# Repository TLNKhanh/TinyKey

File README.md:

# TinyKey

A keychain with 49 LEDs on the front and a ten cent MCU doing the work.

I built this because I wanted to find out how much display you can get out of a
microcontroller that costs less than a coffee. The answer, it turns out, is a
49 LED matrix you can scroll text on, carry in your pocket, and charge from
USB-C. The whole thing runs on a CH32V003, the chip WCH sells for about ten
cents.

## Why a ten cent MCU

The CH32V003F4P6 costs about ten cents and it is a real 32-bit part: RISC-V at
48 MHz, 16 kB flash, 2 kB RAM, 18 GPIOs, UART, I2C, SPI, a 10-bit ADC, all in a
TSSOP-20. No USB, no crystal, no external memory, no display controller.

That is the whole appeal. A 7x7 matrix needs 14 pins and 25 bytes of frame
buffer, and the scan has to keep a fixed frame time or the brightness wobbles.
The chip has just enough of everything, so the money goes into the display
instead of the silicon: no driver IC, no series resistors, and the current limit
is the 2 MHz GPIO drive setting. What you pay in return is software, and for a
keychain that is a good trade.

## V1 or V2?

There are two revisions and they are easy to mix up. The photos are V1, the
files in `hardware/` are V2, and V2 has never been manufactured.

| | V1 | V2 |
|---|---|---|
| Shown in | the photos below | the 3D renders and PDFs |
| Board file | `hardware/archive/TinyKeyV1.kicad_pcb` | `hardware/TinyKey.kicad_pcb` |
| Built | yes, it runs | no, files only |
| Size | 40 x 52 mm | 35 x 45.4 mm |
| What changed | the prototype | tighter outline, ground pours redone, DRC clean |

If you want to order a board, use V2. The photos are just what the thing looks
like assembled, with a cell and a keyring on it.

## The hardware

Front: 49 0805 LEDs wired as 7 anode rows and 7 cathode columns, 14 GPIOs in
total. Back: the MCU, the charger, USB-C (power only, the data pins go nowhere),
two buttons, SWIO pads for programming and B+/B- for the cell. Two layers, no
series resistors.

One thing that bit me: the first batch came back with all 49 LEDs soldered
backwards. Instead of reworking 49 parts I flipped the drive polarity in
firmware, so a lit LED is anode LOW, cathode HIGH. It still works that way.

One trap: BTN1 sits on PD7, which is NRST from the factory. Write the option
bytes (`USER = 0x1F`) or the button reboots the chip instead of changing effect.
The bytes and commands are in
[docs/hardware.md](docs/hardware.md#pd7-is-nrst-by-default).

| Front, 49 LEDs lit | Back, cell taped over the charger |
|---|---|
|  |  |

Everything for ordering: [schematic PDF](docs/hardware/TinyKey-schematic.pdf),
[PCB top](docs/hardware/TinyKey-pcb-top.pdf) and
[bottom](docs/hardware/TinyKey-pcb-bottom.pdf) PDFs,
[gerbers](hardware/gerbers), [fab zip](hardware/TinyKeyV2_gerbers.zip),
[BOM](hardware/bom.csv), KiCad [project](hardware/).

## The software

`firmware/arduino/tinykey_v2` is the current sketch, on the WCH Arduino core. It
scrolls "Hello World" and then nine generated patterns, with 15 step software
PWM per LED so text fades and moves in sub-pixel steps.

`firmware/c` is the smaller ch32v003fun build. One C file, 14 effects, no
Arduino layer, and the one that first ran on the board.

BTN1 steps through the patterns. BTN2 sleeps: the sketch blanks the matrix,
stops the tick and halts the core with `WFI`, and the next press wakes it. There
is no load switch on the board, so that is all the power management there is.

### Build and flash

```bash
# Arduino firmware
arduino-cli compile --fqbn WCH:ch32v:CH32V00x_EVT:pnum=CH32V003F4 \
  --output-dir out firmware/arduino/tinykey_v2
timeout 30 minichlink -w out/tinykey_v2.ino.bin flash -b

# C firmware (riscv-none-elf-gcc, ch32v003fun as a sibling directory)
cd firmware/c
make
make flash
```

There is no USB bootloader, so SWIO and a WCH-Link are the only way in. Prebuilt
binaries are in [prebuilt/](prebuilt/), and the Windows driver setup plus the
option bytes are covered in [docs/flashing.md](docs/flashing.md).

## Repo layout

`firmware/arduino/tinykey_v2/` is the current sketch and `firmware/c/` the
ch32v003fun one. `bringup/` and `firmware/arduino/legacy/` are history.
`hardware/` holds the KiCad project, gerbers, BOM and archived revisions,
`docs/` the pin map, flashing and photo notes, `host/` and `tools/` the WinUSB
helper and flash scripts, `prebuilt/` the binaries.

## Status

V1 works. V2 is files and gerbers, not silicon. The Arduino sketch compiles to
9172 B of 16 kB. The prebuilt binaries came from these sources, but I have not
tried them on anyone else's board.

MIT, see [LICENSE](LICENSE).

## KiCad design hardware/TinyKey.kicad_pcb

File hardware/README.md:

# Hardware

KiCad 10 project for the TinyKey keychain: CH32V003F4P6, a 7x7 LED matrix and a
TP4056 charger on a two-layer board about 35 x 45 mm. Open
`TinyKey.kicad_pro`; the schematic and PCB sit next to it.

| File | What it is |
|---|---|
| `TinyKey.kicad_pro` | project |
| `TinyKey.kicad_sch` | schematic (USB, MCU, buttons, LED matrix, charger) |
| `TinyKey.kicad_pcb` | current board, neck and 5 mm keyring hole |
| `bom.csv` | bill of materials, grouped by value/footprint |
| `gerbers/` | gerbers, job file and PTH/NPTH drills |
| `TinyKeyV2_gerbers.zip` | the same plot zipped for a fab house |
| `archive/` | earlier outlines and revisions |
| `archive/TinyKeyV1.kicad_pcb` | V1, 40 x 52 mm, the board that was built |

## V1 and V2

`TinyKey.kicad_pcb` here is **V2**: 35 x 45.4 mm, tighter outline, ground pours
redone, DRC clean. It has not been manufactured.

The photos in `../docs/images/photo-*.jpg` are **V1**, 40 x 52 mm, the revision
that actually came back from the fab and has all 49 LEDs soldered backwards.
Same circuit, same firmware, bigger board.

## Reading it without KiCad

- `../docs/hardware/TinyKey-schematic.pdf`
- `../docs/hardware/TinyKey-pcb-top.pdf` and `-bottom.pdf`
- `../docs/images/` - schematic PNG and 3D renders
- `../docs/hardware.md` - pin map, option bytes, current limits

## Fabrication notes

- Two layers. The USB-C shell drills are **0.7 mm**, and the board was checked
  with hole clearance at 0.16 mm.
- The neck has a 5 mm hole with 2.5 mm of material between the hole and the
  board edge.
- The LED matrix has **no series resistors**; see `../docs/hardware.md`.
- `BTN1` is on PD7/NRST, so write the option bytes before expecting the button
  to work: `../docs/hardware.md#pd7-is-nrst-by-default`.

DRC is clean apart from harmless warnings: library-footprint mismatches and two
0.7 mm silkscreen texts (the minimum is 0.8 mm). 0 errors, 0 unconnected.

## Renders

The images in `../docs/images/` are generated from the board file, so they stay
in sync:

```bash
kicad-cli pcb render --output docs/images/board-top.png --side top \
  --width 1600 --height 1200 --quality high --background opaque --floor \
  hardware/TinyKey.kicad_pcb
```

The PDFs are exported with `kicad-cli sch export pdf` and
`kicad-cli pcb export pdf` (layers `F.Cu,F.Silkscreen,Edge.Cuts`, and the
mirrored `B.*` set for the bottom).

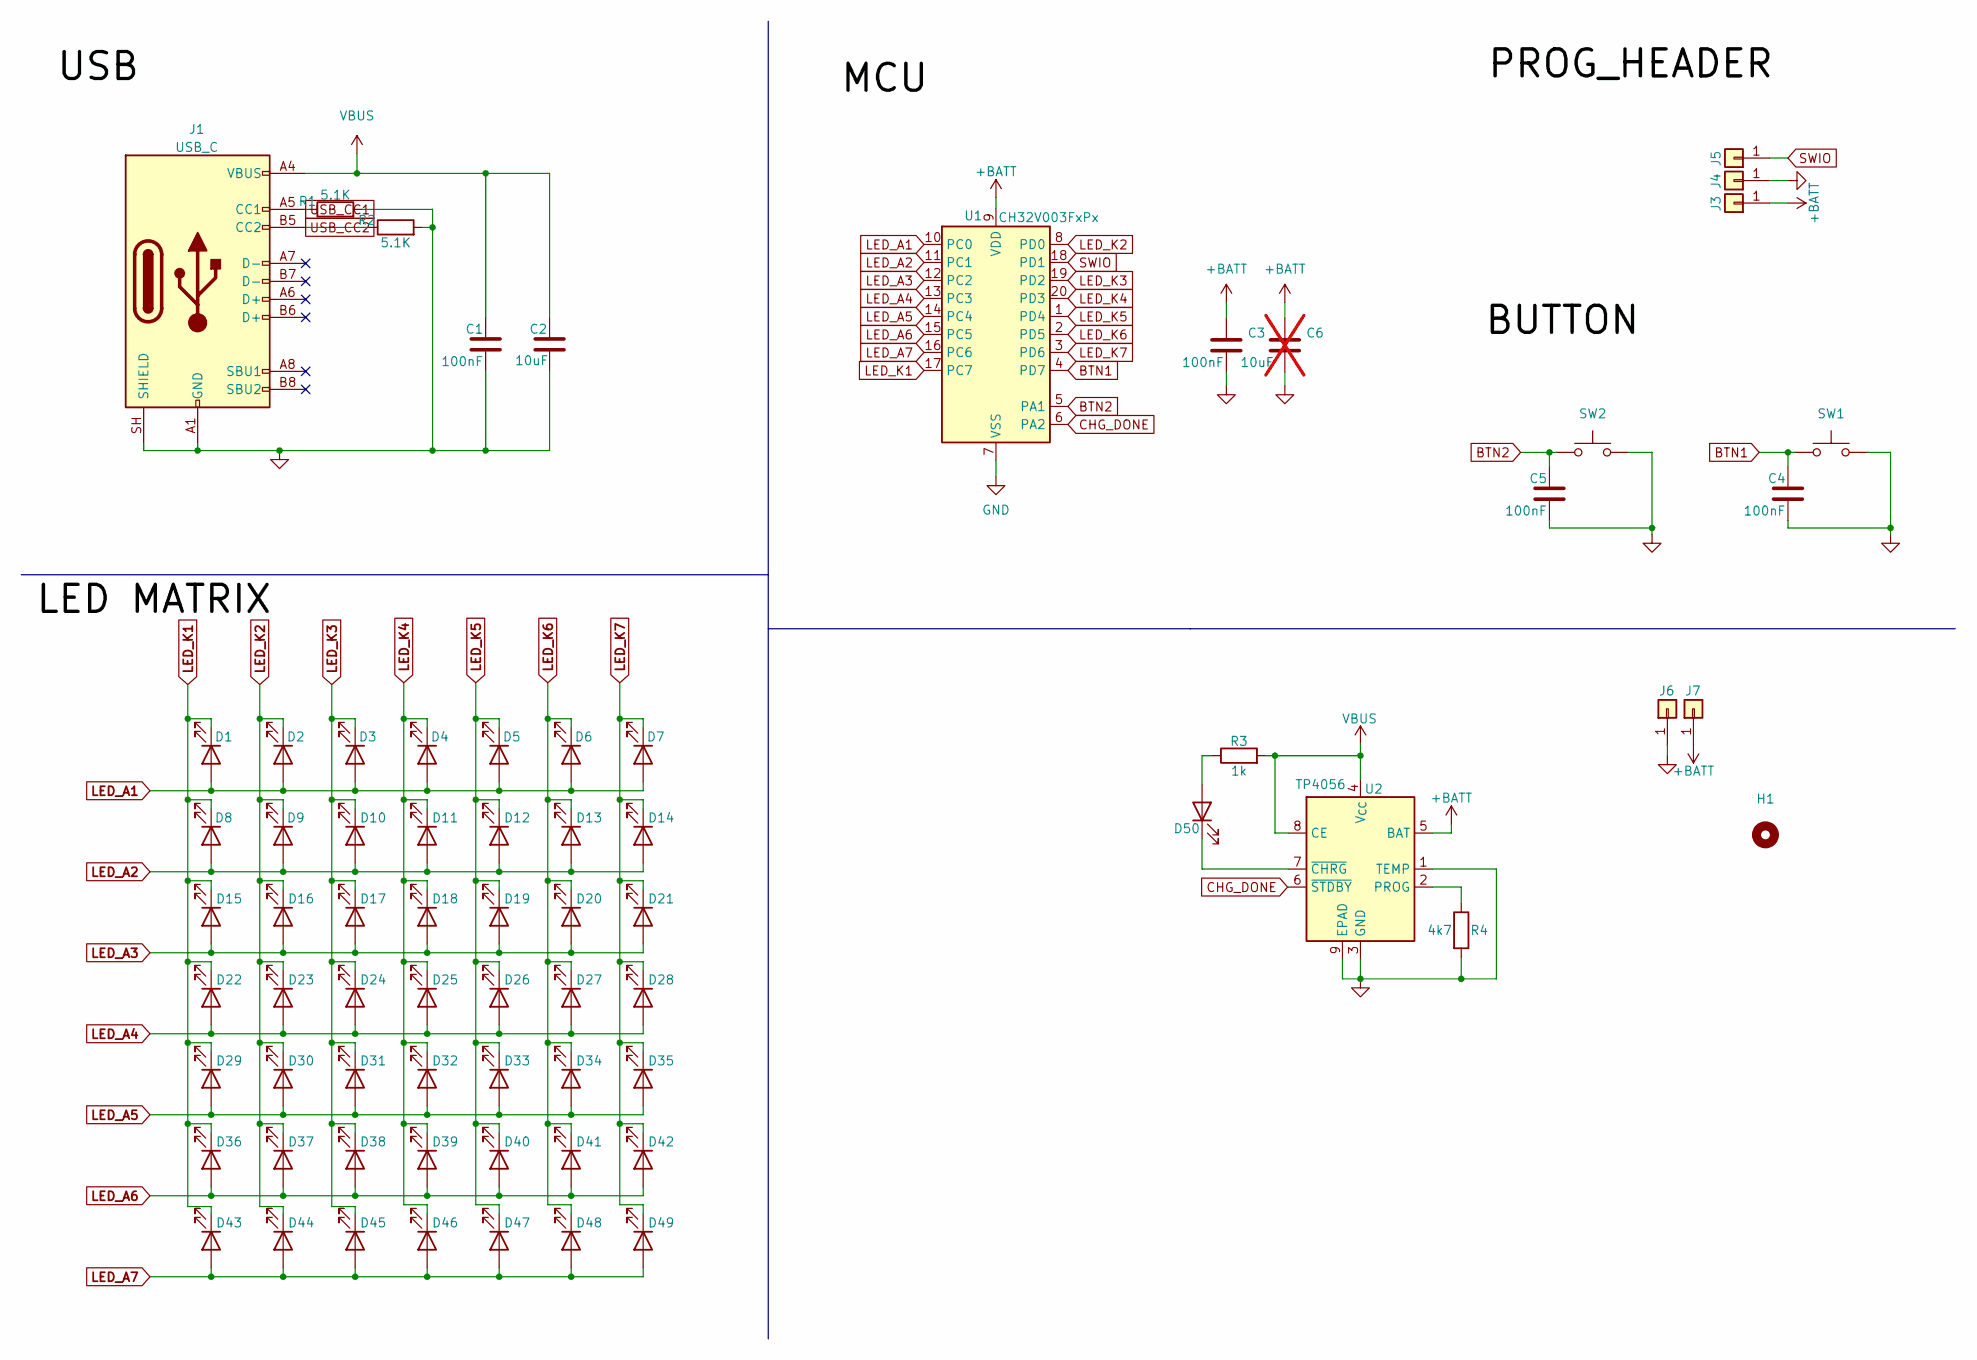
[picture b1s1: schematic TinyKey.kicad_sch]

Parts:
C1, C3, C4, C5: 100nF; C_0603_1608Metric_Pad1.08x0.95mm_HandSolder
C2: 10uF; C_0603_1608Metric_Pad1.08x0.95mm_HandSolder
C6: 10uF; C_0603_1608Metric_Pad1.08x0.95mm_HandSolder; not fitted
D1, D2, D3, D4, D5, D6, D7, D8, D9, D10, D11, D12, D13, D14, D15, D16, D17, D18, D19, D20, D21, D22, D23, D24, D25, D26, D27, D28, D29, D30, D31, D32, D33, D34, D35, D36, D37, D38, D39, D40, D41, D42, D43, D44, D45, D46, D47, D48, D49, D50: LED; LED_0805_2012Metric_Pad1.15x1.40mm_HandSolder
H1: MountingHole_5mm
J1: USB_C; USB_C_Receptacle_GCT_USB4110
J3, J4, J5, J6, J7: Conn_01x01; TestPoint_Pad_D1.0mm
R1, R2: 5.1K; R_0402_1005Metric_Pad0.72x0.64mm_HandSolder
R3: 1k; R_0603_1608Metric_Pad0.98x0.95mm_HandSolder
R4: 4k7; R_0603_1608Metric_Pad0.98x0.95mm_HandSolder
SW1, SW2: SW_Push; SW_Push_1P1T_NO_E-Switch_TL3301NxxxxxG
U1: CH32V003FxPx; TSSOP-20_4.4x6.5mm_P0.65mm
U2: TP4056; SOIC-8-1EP_3.9x4.9mm_P1.27mm_EP2.41x3.81mm

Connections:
+BATT: C3.1, C6.1, J3.1, J7.1 (Pin_1_1), U1.9 (VDD), U2.5 (BAT)
BTN1: C4.1, SW1.1, U1.4 (PD7)
BTN2: C5.1, SW2.1, U1.5 (PA1)
CHG_DONE: U1.6 (PA2), U2.6 (~STDBY)
GND: C1.2, C2.2, C3.2, C4.2, C5.2, C6.2, J1.A1 (GND), J1.A12 (GND), J1.B1 (GND), J1.B12 (GND), J1.SH (SHIELD), J4.1, J6.1 (Pin_1_1), R1.2, R2.2, R4.2, SW1.2, SW2.2, U1.7 (VSS), U2.1 (TEMP), U2.3 (GND), U2.9 (EPAD)
LED_A1: D1.2 (A), D2.2 (A), D3.2 (A), D4.2 (A), D5.2 (A), D6.2 (A), D7.2 (A), U1.10 (PC0)
LED_A2: D8.2 (A), D9.2 (A), D10.2 (A), D11.2 (A), D12.2 (A), D13.2 (A), D14.2 (A), U1.11 (PC1)
LED_A3: D15.2 (A), D16.2 (A), D17.2 (A), D18.2 (A), D19.2 (A), D20.2 (A), D21.2 (A), U1.12 (PC2)
LED_A4: D22.2 (A), D23.2 (A), D24.2 (A), D25.2 (A), D26.2 (A), D27.2 (A), D28.2 (A), U1.13 (PC3)
LED_A5: D29.2 (A), D30.2 (A), D31.2 (A), D32.2 (A), D33.2 (A), D34.2 (A), D35.2 (A), U1.14 (PC4)
LED_A6: D36.2 (A), D37.2 (A), D38.2 (A), D39.2 (A), D40.2 (A), D41.2 (A), D42.2 (A), U1.15 (PC5)
LED_A7: D43.2 (A), D44.2 (A), D45.2 (A), D46.2 (A), D47.2 (A), D48.2 (A), D49.2 (A), U1.16 (PC6)
LED_K1: D1.1 (K), D8.1 (K), D15.1 (K), D22.1 (K), D29.1 (K), D36.1 (K), D43.1 (K), U1.17 (PC7)
LED_K2: D2.1 (K), D9.1 (K), D16.1 (K), D23.1 (K), D30.1 (K), D37.1 (K), D44.1 (K), U1.8 (PD0)
LED_K3: D3.1 (K), D10.1 (K), D17.1 (K), D24.1 (K), D31.1 (K), D38.1 (K), D45.1 (K), U1.19 (PD2)
LED_K4: D4.1 (K), D11.1 (K), D18.1 (K), D25.1 (K), D32.1 (K), D39.1 (K), D46.1 (K), U1.20 (PD3)
LED_K5: D5.1 (K), D12.1 (K), D19.1 (K), D26.1 (K), D33.1 (K), D40.1 (K), D47.1 (K), U1.1 (PD4)
LED_K6: D6.1 (K), D13.1 (K), D20.1 (K), D27.1 (K), D34.1 (K), D41.1 (K), D48.1 (K), U1.2 (PD5)
LED_K7: D7.1 (K), D14.1 (K), D21.1 (K), D28.1 (K), D35.1 (K), D42.1 (K), D49.1 (K), U1.3 (PD6)
unnamed: D50.2 (A), R3.1
unnamed: D50.1 (K), U2.7 (~CHRG)
unnamed: R4.1, U2.2 (PROG)
SWIO: J5.1 (Pin_1_1), U1.18 (PD1)
USB_CC1: J1.A5 (CC1), R1.1
USB_CC2: J1.B5 (CC2), R2.1
VBUS: C1.1, C2.1, J1.A4 (VBUS), J1.A9 (VBUS), J1.B4 (VBUS), J1.B9 (VBUS), R3.2, U2.4 (V_{CC}), U2.8 (CE)

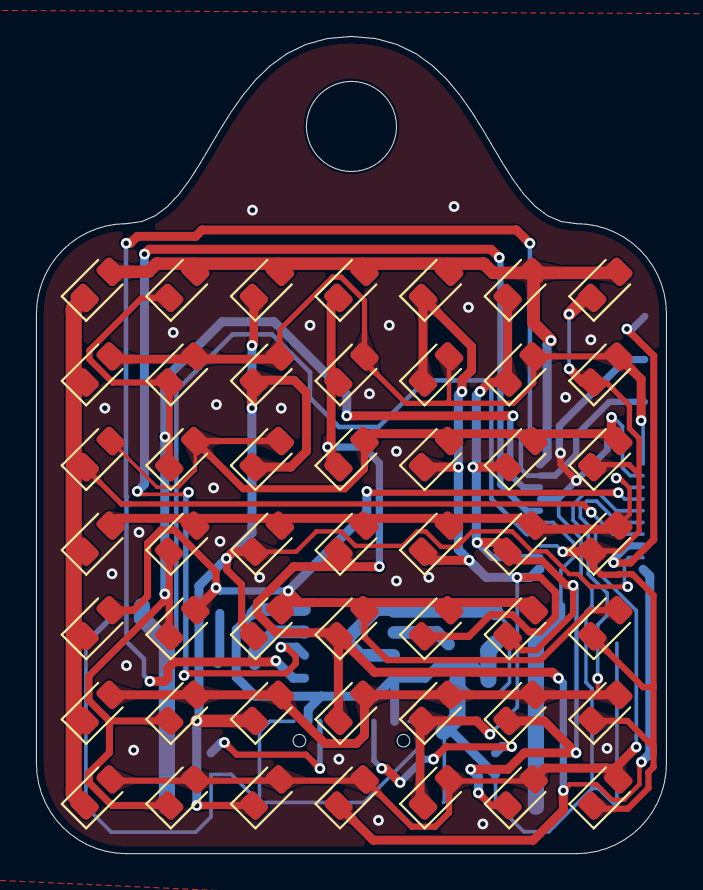
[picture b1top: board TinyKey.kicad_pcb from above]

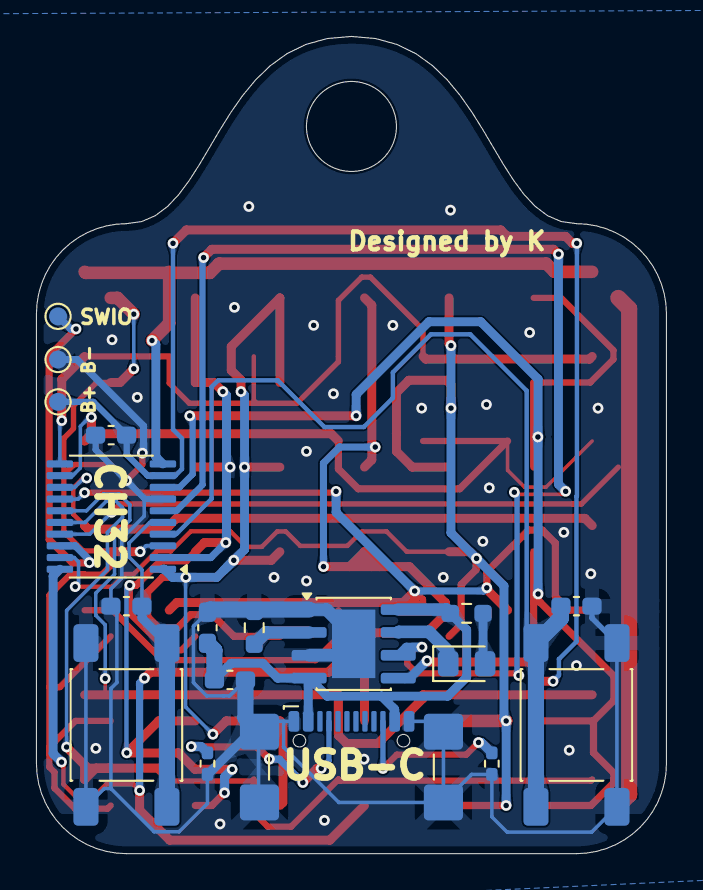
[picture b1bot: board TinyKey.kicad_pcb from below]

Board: 2 copper layers, 35.0 x 45.4 mm, 68 parts (18 on the bottom side), 26 nets.

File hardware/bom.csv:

"Refs","Value","Footprint","Qty","DNP"
"C1,C3-C5","100nF","Capacitor_SMD:C_0603_1608Metric_Pad1.08x0.95mm_HandSolder","4",""
"C2","10uF","Capacitor_SMD:C_0603_1608Metric_Pad1.08x0.95mm_HandSolder","1",""
"D1-D50","LED","LED_SMD:LED_0805_2012Metric_Pad1.15x1.40mm_HandSolder","50",""
"J1","USB_C","Connector_USB:USB_C_Receptacle_GCT_USB4110","1",""
"J3,J5-J7","Conn_01x01","TestPoint:TestPoint_Pad_D1.0mm","4",""
"R1,R2","5.1K","Resistor_SMD:R_0402_1005Metric_Pad0.72x0.64mm_HandSolder","2",""
"R3","1k","Resistor_SMD:R_0603_1608Metric_Pad0.98x0.95mm_HandSolder","1",""
"R4","4k7","Resistor_SMD:R_0603_1608Metric_Pad0.98x0.95mm_HandSolder","1",""
"SW1,SW2","SW_Push","Button_Switch_SMD:SW_Push_1P1T_NO_E-Switch_TL3301NxxxxxG","2",""
"U1","CH32V003FxPx","Package_SO:TSSOP-20_4.4x6.5mm_P0.65mm","1",""
"U2","TP4056","Package_SO:SOIC-8-1EP_3.9x4.9mm_P1.27mm_EP2.41x3.81mm","1",""

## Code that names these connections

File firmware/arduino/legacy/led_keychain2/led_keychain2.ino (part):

/*
 * 7x7 multiplexed LED keychain - CH32V003 (Arduino core)
 *   Text: "Nam Khanh"  + 14 effects
 *   BTN1 (PD7) = next effect     BTN2 (PA1) = sleep / wake
 *
 * Wiring:
 *   Anodes   A1..A7 = PC0..PC6
 *   Cathodes K1..K7 = PC7, PD0, PD2, PD3, PD4, PD5, PD6
 *   BTN1 = PD7 (NRST disabled via option byte USER=0x1F)
 *   BTN2 = PA1 (active low, internal pull-up, 100nF to GND)
 *   PA2  = TP4056 charge status (not used in firmware)
 *   PD1  = SWIO (never touched)
 *
 * POLARITY: LEDs soldered backwards -> lit = anode LOW + cathode HIGH.
 * CURRENT: no series resistors -> 2 MHz GPIO drive only.
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void setup() {
    RCC->APB2PCENR |= (1u << 2) | (1u << 4) | (1u << 5);
    blankAll();
    // buttons: PD7 and PA1, pull-up
    GPIOD->CFGLR = (GPIOD->CFGLR & ~NIB(7)) | (CFG_PU << 28);
    GPIOD->OUTDR |= (1u << 7);
    GPIOA->CFGLR = (GPIOA->CFGLR & ~(NIB(1))) | (CFG_PU << 4);
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
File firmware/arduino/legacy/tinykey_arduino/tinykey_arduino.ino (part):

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//          Arduino IDE: Tools > Board > CH32 MCU EVT Boards > CH32V00x
//
//  7x7 multiplexed LED matrix D1..D49 on 14 GPIO lines:
//    anode   A1..A7 -> PC0..PC6
//    cathode K1..K7 -> PC7, PD0, PD2, PD3, PD4, PD5, PD6
//  D_n -> row = (n-1)/7 (anode line), col = (n-1)%7 (cathode line)
//
//  All 49 front LEDs are soldered in BACKWARDS, so the drive polarity is
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//     matrix for exactly this reason; the 2 MHz nibble is written directly.)
//
//  Buttons (switches to GND, internal pull-up, active low):
//    PD7 -> next effect
//    PA1 -> sleep / wake
//
//  PD7 is also NRST. The reset function MUST be disabled in the option bytes
//  (USER bits 3-4 = 11), otherwise pressing this button resets the chip
//  instead of switching effect. Already done on this board -- see README.md.
// ============================================================================
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// ---------------------------------------------------------------------------
//  Pin map (Arduino pin names from variant_CH32V003F4.h)
// ---------------------------------------------------------------------------
static const uint8_t ANODE_PIN[7] = { PC0, PC1, PC2, PC3, PC4, PC5, PC6 };
static const uint8_t CATH_PIN [7] = { PC7, PD0, PD2, PD3, PD4, PD5, PD6 };

#define BTN_FX  PD7   // next effect
#define BTN_SLP PA1   // sleep / wake

#define ST_HZ 0
#define ST_HI 1
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        break;

    case FX_BTNTEST:                        // diagnostics: which button is held
        if(digitalRead(BTN_FX)  == LOW) fb_set(0,0);   // D1  top-left  = PD7
        if(digitalRead(BTN_SLP) == LOW) fb_set(0,6);   // D7  top-right = PA1
        if(digitalRead(BTN_FX)==LOW && digitalRead(BTN_SLP)==LOW) fb_set(6,6);
        break;
    }
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    // The Arduino core only switches a GPIO port's clock on when a pin on that
    // port is first used (set_GPIO_Port_Clock in PortNames.c, called from
    // pinMode). This sketch drives the matrix by direct register access, so
    // pinMode() is never called on a PC pin -- and ALL 7 anode lines (PC0..PC6)
    // plus cathode K1 (PC7) live on GPIOC. Without this line GPIOC stays
    // clockless, every write to it is ignored, and the matrix is completely
    // dark. (The ch32v003fun firmware had the same enable in main().)
    RCC->APB2PCENR |= RCC_APB2Periph_GPIOA | RCC_APB2Periph_GPIOC | RCC_APB2Periph_GPIOD;
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    // (the SysTick NVIC enable that pre_init() did stays in force)

    all_lines_hz();
    pinMode(BTN_FX,  INPUT_PULLUP);   // PD7
    pinMode(BTN_SLP, INPUT_PULLUP);   // PA1

    last = slast = millis();
}
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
